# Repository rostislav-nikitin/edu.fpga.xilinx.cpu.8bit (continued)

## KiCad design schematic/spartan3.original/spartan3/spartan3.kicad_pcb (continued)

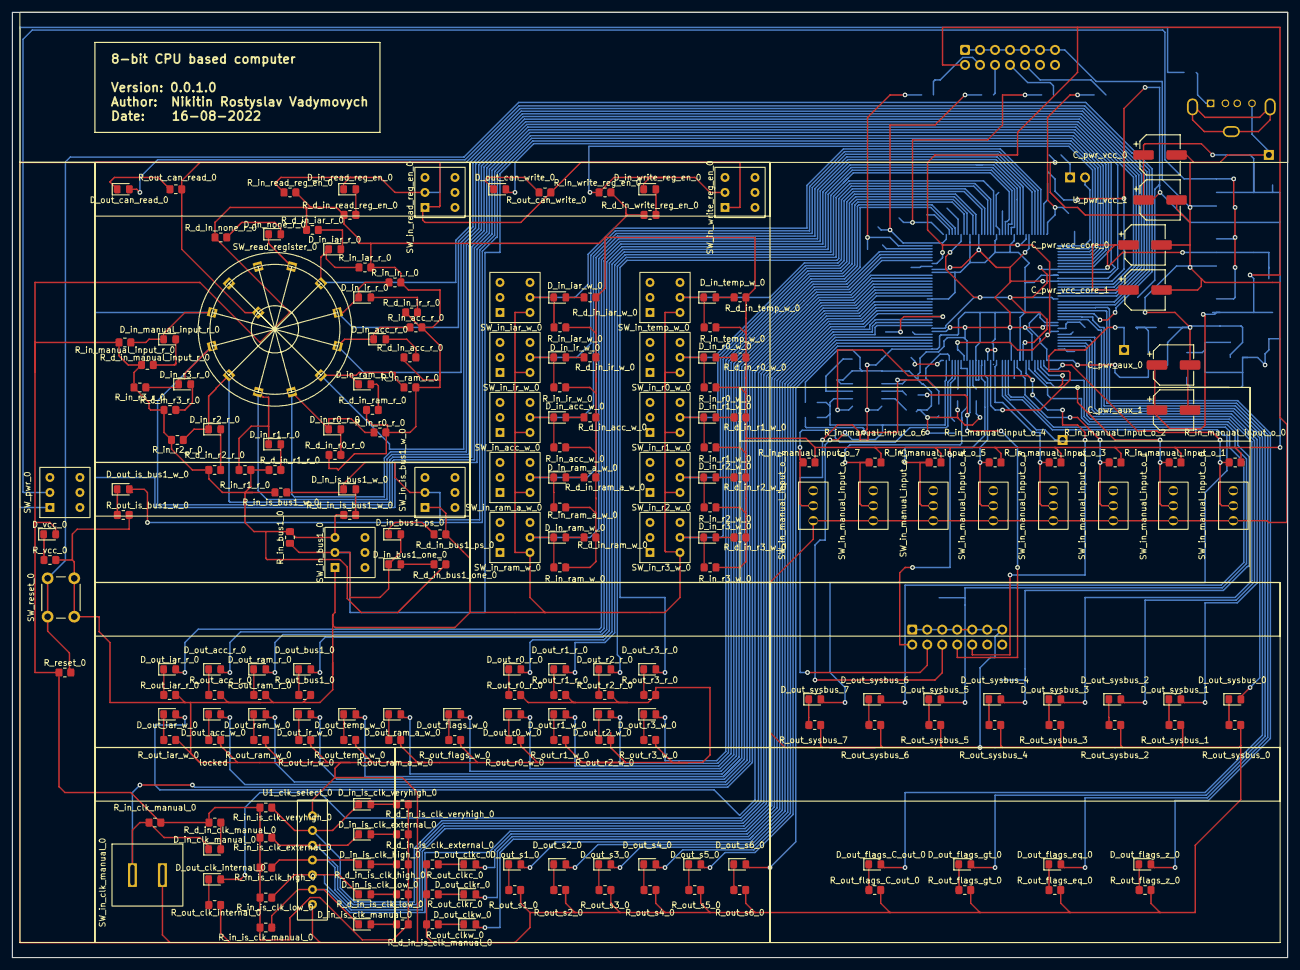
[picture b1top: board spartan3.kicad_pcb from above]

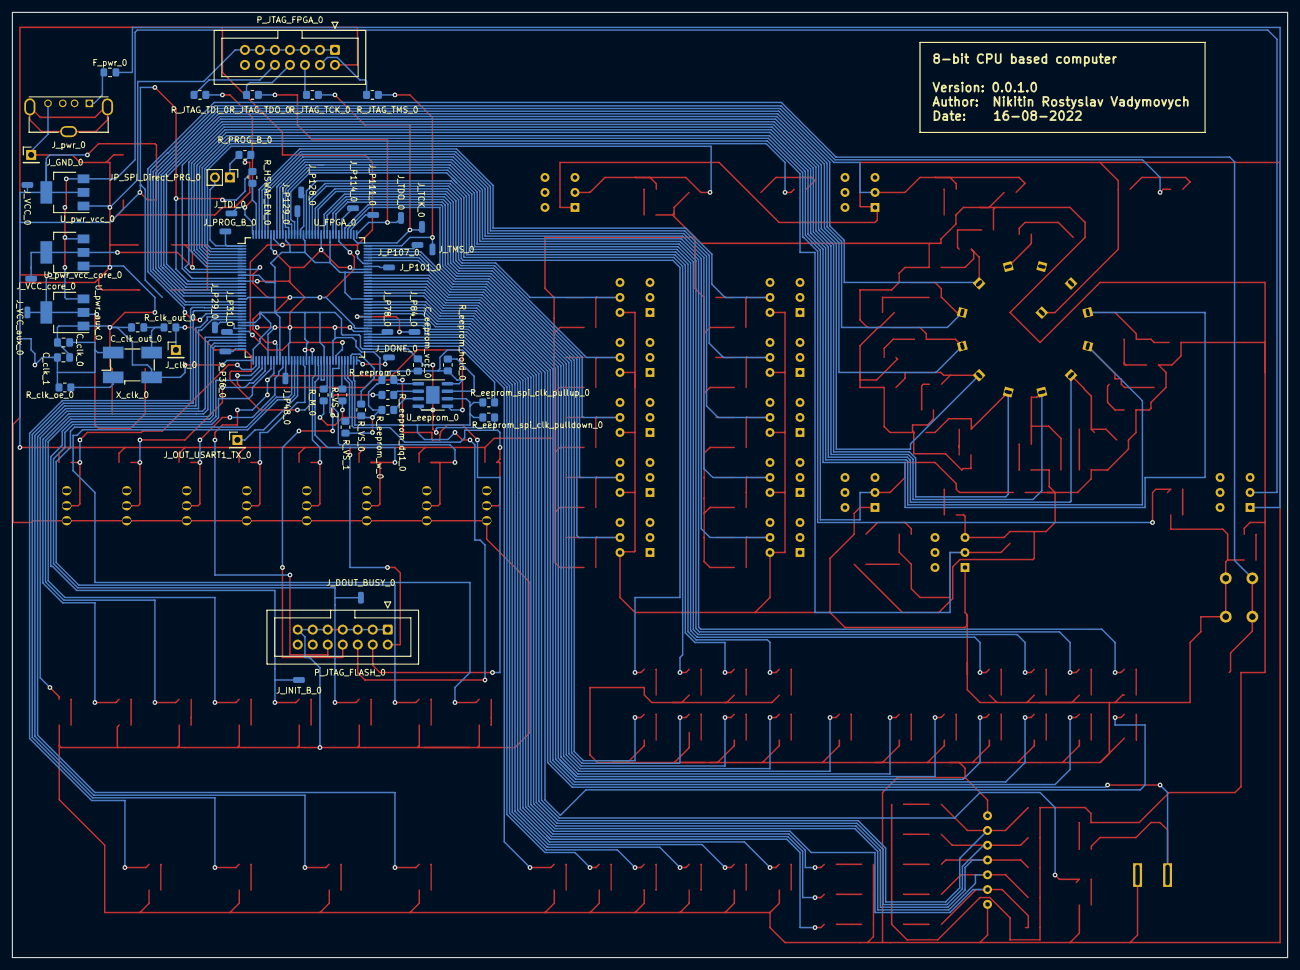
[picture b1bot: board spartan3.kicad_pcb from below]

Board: 2 copper layers, 215.9 x 160.0 mm, 282 parts (59 on the bottom side), 205 nets.

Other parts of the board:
locked: 68R; R_0805_2012Metric_Pad1.20x1.40mm_HandSolder

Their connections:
GND: locked.2; also elsewhere on the board
unnamed 42: locked.1; also elsewhere on the board

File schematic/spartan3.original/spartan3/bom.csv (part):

"null","Sourced","Placed","References","Value","Footprint"
1,"✓","","C_clk_out_0","15pF","C_0805_2012Metric_Pad1.18x1.45mm_HandSolder"
2,"✓","","C_clk_0","0.1uF","C_0805_2012Metric_Pad1.18x1.45mm_HandSolder"
3,"✓","","C_clk_1","4.7uF","C_0805_2012Metric_Pad1.18x1.45mm_HandSolder"
4,"✓","","C_pwr_aux_0","100uF","CP_Elec_6.3x5.4"
5,"✓","","C_pwr_aux_1","100uF","CP_Elec_6.3x5.4"
6,"✓","","C_pwr_vcc_0","100uF","CP_Elec_6.3x5.4"
7,"✓","","C_pwr_vcc_core_0","100uF","CP_Elec_6.3x5.4"
8,"✓","","C_pwr_vcc_core_1","100uF","CP_Elec_6.3x5.4"
9,"✓","","U_pwr_vcc_1","100uF","CP_Elec_6.3x5.4"
10,"✓","","R__eeprom_dq1_0","33R","R_0805_2012Metric_Pad1.20x1.40mm_HandSolder"
11,"✓","","R_clk_out_0","33R","R_0805_2012Metric_Pad1.20x1.40mm_HandSolder"
12,"✓","","R_JTAG_TCK_0","33R","R_0805_2012Metric_Pad1.20x1.40mm_HandSolder"
13,"✓","","R_JTAG_TDI_0","33R","R_0805_2012Metric_Pad1.20x1.40mm_HandSolder"
14,"✓","","R_JTAG_TDO_0","33R","R_0805_2012Metric_Pad1.20x1.40mm_HandSolder"
15,"✓","","R_JTAG_TMS_0","33R","R_0805_2012Metric_Pad1.20x1.40mm_HandSolder"
16,"✓","","R_d_in_acc_r_0","68R","R_0805_2012Metric_Pad1.20x1.40mm_HandSolder"
17,"✓","","R_d_in_acc_w_0","68R","R_0805_2012Metric_Pad1.20x1.40mm_HandSolder"
18,"✓","","R_d_in_bus1_one_0","68R","R_0805_2012Metric_Pad1.20x1.40mm_HandSolder"
19,"✓","","R_d_in_bus1_ps_0","68R","R_0805_2012Metric_Pad1.20x1.40mm_HandSolder"
20,"✓","","R_d_in_clk_manual_0","68R","R_0805_2012Metric_Pad1.20x1.40mm_HandSolder"
21,"✓","","R_d_in_iar_r_0","68R","R_0805_2012Metric_Pad1.20x1.40mm_HandSolder"
22,"✓","","R_d_in_iar_w_0","68R","R_0805_2012Metric_Pad1.20x1.40mm_HandSolder"
23,"✓","","R_d_in_ir_r_0","68R","R_0805_2012Metric_Pad1.20x1.40mm_HandSolder"
24,"✓","","R_d_in_ir_w_0","68R","R_0805_2012Metric_Pad1.20x1.40mm_HandSolder"
25,"✓","","R_d_in_is_bus1_w_0","68R","R_0805_2012Metric_Pad1.20x1.40mm_HandSolder"
26,"✓","","R_d_in_is_clk_external_0","68R","R_0805_2012Metric_Pad1.20x1.40mm_HandSolder"
27,"✓","","R_d_in_is_clk_high_0","68R","R_0805_2012Metric_Pad1.20x1.40mm_HandSolder"
28,"✓","","R_d_in_is_clk_low_0","68R","R_0805_2012Metric_Pad1.20x1.40mm_HandSolder"
29,"✓","","R_d_in_is_clk_manual_0","68R","R_0805_2012Metric_Pad1.20x1.40mm_HandSolder"
30,"✓","","R_d_in_is_clk_veryhigh_0","68R","R_0805_2012Metric_Pad1.20x1.40mm_HandSolder"
31,"✓","","R_d_in_manual_input_r_0","68R","R_0805_2012Metric_Pad1.20x1.40mm_HandSolder"
32,"✓","","R_d_in_none_r_0","68R","R_0805_2012Metric_Pad1.20x1.40mm_HandSolder"
33,"✓","","R_d_in_r0_r_0","68R","R_0805_2012Metric_Pad1.20x1.40mm_HandSolder"
34,"✓","","R_d_in_r0_w_0","68R","R_0805_2012Metric_Pad1.20x1.40mm_HandSolder"
35,"✓","","R_d_in_r1_r_0","68R","R_0805_2012Metric_Pad1.20x1.40mm_HandSolder"
36,"✓","","R_d_in_r1_w_0","68R","R_0805_2012Metric_Pad1.20x1.40mm_HandSolder"
37,"✓","","R_d_in_r2_r_0","68R","R_0805_2012Metric_Pad1.20x1.40mm_HandSolder"
38,"✓","","R_d_in_r2_w_0","68R","R_0805_2012Metric_Pad1.20x1.40mm_HandSolder"
39,"✓","","R_d_in_r3_r_0","68R","R_0805_2012Metric_Pad1.20x1.40mm_HandSolder"
40,"✓","","R_d_in_r3_w_0","68R","R_0805_2012Metric_Pad1.20x1.40mm_HandSolder"
41,"✓","","R_d_in_ram_a_w_0","68R","R_0805_2012Metric_Pad1.20x1.40mm_HandSolder"
42,"✓","","R_d_in_ram_r_0","68R","R_0805_2012Metric_Pad1.20x1.40mm_HandSolder"
43,"✓","","R_d_in_ram_w_0","68R","R_0805_2012Metric_Pad1.20x1.40mm_HandSolder"
44,"✓","","R_d_in_read_reg_en_0","68R","R_0805_2012Metric_Pad1.20x1.40mm_HandSolder"
45,"✓","","R_d_in_temp_w_0","68R","R_0805_2012Metric_Pad1.20x1.40mm_HandSolder"
46,"✓","","R_d_in_write_reg_en_0","68R","R_0805_2012Metric_Pad1.20x1.40mm_HandSolder"
47,"✓","","R_out_acc_r_0","68R","R_0805_2012Metric_Pad1.20x1.40mm_HandSolder"
48,"✓","","R_out_acc_w_0","68R","R_0805_2012Metric_Pad1.20x1.40mm_HandSolder"
49,"✓","","R_out_bus1_0","68R","R_0805_2012Metric_Pad1.20x1.40mm_HandSolder"
50,"✓","","R_out_can_read_0","68R","R_0805_2012Metric_Pad1.20x1.40mm_HandSolder"
51,"✓","","R_out_can_write_0","68R","R_0805_2012Metric_Pad1.20x1.40mm_HandSolder"
52,"✓","","R_out_clk_internal_0","68R","R_0805_2012Metric_Pad1.20x1.40mm_HandSolder"
53,"✓","","R_out_clkc_0","68R","R_0805_2012Metric_Pad1.20x1.40mm_HandSolder"
54,"✓","","R_out_clkr_0","68R","R_0805_2012Metric_Pad1.20x1.40mm_HandSolder"
55,"✓","","R_out_clkw_0","68R","R_0805_2012Metric_Pad1.20x1.40mm_HandSolder"
56,"✓","","R_out_flags_C_out_0","68R","R_0805_2012Metric_Pad1.20x1.40mm_HandSolder"
57,"✓","","R_out_flags_eq_0","68R","R_0805_2012Metric_Pad1.20x1.40mm_HandSolder"
58,"✓","","R_out_flags_gt_0","68R","R_0805_2012Metric_Pad1.20x1.40mm_HandSolder"
59,"✓","","R_out_flags_w_0","68R","R_0805_2012Metric_Pad1.20x1.40mm_HandSolder"
60,"✓","","R_out_flags_z_0","68R","R_0805_2012Metric_Pad1.20x1.40mm_HandSolder"
61,"✓","","R_out_iar_r_0","68R","R_0805_2012Metric_Pad1.20x1.40mm_HandSolder"
62,"✓","","R_out_iar_w_0","68R","R_0805_2012Metric_Pad1.20x1.40mm_HandSolder"
63,"✓","","R_out_ir_w_0","68R","R_0805_2012Metric_Pad1.20x1.40mm_HandSolder"
64,"✓","","R_out_is_bus1_w_0","68R","R_0805_2012Metric_Pad1.20x1.40mm_HandSolder"
65,"✓","","R_out_r0_r_0","68R","R_0805_2012Metric_Pad1.20x1.40mm_HandSolder"
66,"✓","","R_out_r0_w_0","68R","R_0805_2012Metric_Pad1.20x1.40mm_HandSolder"
67,"✓","","R_out_r1_r_0","68R","R_0805_2012Metric_Pad1.20x1.40mm_HandSolder"
68,"✓","","R_out_r1_w_0","68R","R_0805_2012Metric_Pad1.20x1.40mm_HandSolder"
69,"✓","","R_out_r2_r_0","68R","R_0805_2012Metric_Pad1.20x1.40mm_HandSolder"
70,"✓","","R_out_r2_w_0","68R","R_0805_2012Metric_Pad1.20x1.40mm_HandSolder"
71,"✓","","R_out_r3_r_0","68R","R_0805_2012Metric_Pad1.20x1.40mm_HandSolder"
72,"✓","","R_out_r3_w_0","68R","R_0805_2012Metric_Pad1.20x1.40mm_HandSolder"
73,"✓","","R_out_ram_a_w_0","68R","R_0805_2012Metric_Pad1.20x1.40mm_HandSolder"
74,"✓","","R_out_ram_r_0","68R","R_0805_2012Metric_Pad1.20x1.40mm_HandSolder"
75,"✓","","R_out_ram_w_0","68R","R_0805_2012Metric_Pad1.20x1.40mm_HandSolder"
76,"✓","","R_out_s1_0","68R","R_0805_2012Metric_Pad1.20x1.40mm_HandSolder"
77,"✓","","R_out_s2_0","68R","R_0805_2012Metric_Pad1.20x1.40mm_HandSolder"
78,"✓","","R_out_s3_0","68R","R_0805_2012Metric_Pad1.20x1.40mm_HandSolder"
79,"✓","","R_out_s4_0","68R","R_0805_2012Metric_Pad1.20x1.40mm_HandSolder"
80,"✓","","R_out_s5_0","68R","R_0805_2012Metric_Pad1.20x1.40mm_HandSolder"
81,"✓","","R_out_s6_0","68R","R_0805_2012Metric_Pad1.20x1.40mm_HandSolder"
82,"✓","","R_out_sysbus_0","68R","R_0805_2012Metric_Pad1.20x1.40mm_HandSolder"
83,"✓","","R_out_sysbus_1","68R","R_0805_2012Metric_Pad1.20x1.40mm_HandSolder"
84,"✓","","R_out_sysbus_2","68R","R_0805_2012Metric_Pad1.20x1.40mm_HandSolder"
85,"✓","","R_out_sysbus_3","68R","R_0805_2012Metric_Pad1.20x1.40mm_HandSolder"
86,"✓","","R_out_sysbus_4","68R","R_0805_2012Metric_Pad1.20x1.40mm_HandSolder"
87,"✓","","R_out_sysbus_5","68R","R_0805_2012Metric_Pad1.20x1.40mm_HandSolder"
88,"✓","","R_out_sysbus_6","68R","R_0805_2012Metric_Pad1.20x1.40mm_HandSolder"
89,"✓","","R_out_sysbus_7","68R","R_0805_2012Metric_Pad1.20x1.40mm_HandSolder"
90,"✓","","R_out_temp_w_0","68R","R_0805_2012Metric_Pad1.20x1.40mm_HandSolder"
91,"✓","","R_vcc_0","68R","R_0805_2012Metric_Pad1.20x1.40mm_HandSolder"
92,"✓","","R_eeprom_spi_clk_pulldown_0","100R","R_0805_2012Metric_Pad1.20x1.40mm_HandSolder"
93,"✓","","R_eeprom_spi_clk_pullup_0","100R","R_0805_2012Metric_Pad1.20x1.40mm_HandSolder"
94,"✓","","R_PROG_B_0","820R","R_0805_2012Metric_Pad1.20x1.40mm_HandSolder"
95,"✓","","C_eeprom_vcc_0",104,"C_0805_2012Metric_Pad1.18x1.45mm_HandSolder"
96,"✓","","R_eeprom_hold_0","10K","R_0805_2012Metric_Pad1.20x1.40mm_HandSolder"
97,"✓","","R_eeprom_s_0","10K","R_0805_2012Metric_Pad1.20x1.40mm_HandSolder"
98,"✓","","R_eeprom_w_0","10K","R_0805_2012Metric_Pad1.20x1.40mm_HandSolder"
99,"✓","","R_HSWAP_EN_0","10K","R_0805_2012Metric_Pad1.20x1.40mm_HandSolder"
100,"✓","","R_M_0","10K","R_0805_2012Metric_Pad1.20x1.40mm_HandSolder"
101,"✓","","R_VS_0","10K","R_0805_2012Metric_Pad1.20x1.40mm_HandSolder"
102,"✓","","R_VS_1","10K","R_0805_2012Metric_Pad1.20x1.40mm_HandSolder"
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
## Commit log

2022-03-28 Initial
2022-03-30 01. Registers refactored 02. LD/ST instructions implemented (not tested yet)
2022-03-31 LDC instruction implemented
2022-04-01 JMPR/JMP implemented
2022-04-02 JMPIF/CLF instructions was added
2022-04-03 01. Carry in implemented 02. ASM simple counter program implemented
2022-04-04 01. ASM counter program was updated. 02. JMPIF fixed
2022-04-08 Z buffers replaced with MUXERS. Design working in hardware
2022-04-12 Computer front panel was added
2022-04-13 Computer front panel was updated
2022-04-16 Simple cpu frequency divider was implemented
2022-04-16 Divider equation was updated
2022-04-18 Manual R0 implemented
2022-04-19 manr register support was added
2022-04-20 r0, r1, r2, r3 registers r/w updated
2022-04-21 Read/Write blocks implementation done
2022-04-21 CPU testbench updated
2022-04-22 Debug outputs was added
2022-04-24 VGA test driver was implemented
2022-04-24 VGA v2 driver was implemented
2022-04-26 Input/Output CPU PINs was renamed in a same way
2022-04-27 Manual::OK
2022-04-27 Updated to workin state
2022-04-27 Rebuid part of ICs [Working]
2022-04-28 Rebuid part of ICs/added clkc, clkr, clkw to the output [Working]
2022-04-28 Manual/Low Frequency modes was implemented [Working]
2022-05-03 Front panel design updated. Real dimesions was applied.
2022-05-03 3D box model added
2022-05-05 The front panel was updated
2022-05-08 Frontend panel updated
2022-05-10 The frontend panel updated
2022-05-12 01. The frontend panel design was updated 02. The frontend panel 3D STL model was added
2022-05-16 Frontend updated
2022-05-18 Front panel :: Small chages
2022-05-22 Working ver
2022-05-22 Working version :: Stage LEDs was added
2022-05-22 Working version :: Clock mode LEDs and manual button was added
2022-05-24 Working version :: Flags LEDs was added
2022-05-25 Working version :: Sysbus LEDs was added
2022-05-31 Working version :: Read Register block was added
2022-06-01 Working version :: CPU Control block LEDs was added
2022-06-02 Working version :: input switches was added
2022-06-03 Working version :: input switches and logic was added
2022-06-07 Working version :: Write register and bus1 LEDs was added
2022-06-07 Working version :: Writeto RAM and manual clock input debouncing was added
2022-06-08 Working version :: 1Hz/1Stg/1Inst frequency dividers was implemented & added
2022-06-09 Working version :: 1KHz frequency dividers was implemented & added
2022-06-09 Working version :: IR read implemented
2022-06-12 Working version :: Cpu control/Stepper reset was added
2022-06-12 Working version :: Dark front panel was added. Bright front panel was updated
2022-06-13 Not workin Commited
2022-06-13 Working :: version 0.1 alpha
2022-06-20 USART example was added
2022-06-20 Working :: USART was added
2022-06-21 Working :: Prepared to RAM extraction from CPU. Ports support was added
2022-06-21 Working :: RAM extracted
2022-06-22 Working :: Port one added
2022-06-22 Working :: Generator was replaced to counter based one. Port one was fixed
2022-06-24 Working :: PT/One was replaced with PT/Const
2022-06-24 Working(*) :: IN/OUT implemented
2022-06-24 Working :: IN/OUT implemented. Counter updated
2022-06-25 Working :: IN/OUT fixed. ADD 0xF0 was replaced to OR 0xF0
2022-06-25 Working :: Counter updated :: IN added
2022-06-25 Working :: Instruction set extended
2022-07-11 XC3S250E-4TQG144 version KiCAD schematics added
2022-07-12 1.CPU control & Clock blocks added. 2.Slider switch library added.
2022-07-13 Schematics :: Read Register block added
2022-07-14 Schematics :: 1.Write Register added 2.1/PS Bus added
2022-07-16 Schematic :: Power/Clock/JTAG/EEPROM schematics added
2022-07-16 Schematic :: LEDs polarity fixed/Power LED added
2022-07-18 Schematics :: footprints partially assigned
2022-07-19 Schematics :: SW Rotary 12 footprint added
2022-07-20 Schematics :: JTAG/SPST/SPDT updated
2022-07-20 Schematics :: reset added
2022-07-21 PCB layout :: Implementation process started
2022-07-22 PCB layout :: updated
2022-07-26 Schematics :: Read Register fixed -- Rs added. PCB layout :: Updated
2022-07-27 PCB layout :: reset button side swapped
2022-07-27 Schematics :: updated / PCB layout :: updated
2022-07-29 PCB layout updated
2022-08-01 PCB layout :: checked & updated
2022-08-02 Schematic :: LED R/SW_DPDT updated. PCB layout :: logic, non FPGA connections implemented
2022-08-03 Schematics :: J_CONTROL added. PCB layout :: updated
2022-08-05 Schematics :: in/out pins mapped. PCB layout :: updated
2022-08-07 Schematics :: updated. PCB layout :: updated
2022-08-09 FPGA pins mapping added/updated. Schematics/PCB layout :: updated according to the added/updated PINs mapping
2022-08-10 Tactile switch footprint updated. DRC rules checked/fixed
2022-08-10 Schematics :: power capicators added. PCB layout :: labels updated
2022-08-12 Schematics/PCB layout :: Oscilator updated, helpful PINs extracted
2022-08-15 Schematics/PCB layout/FPGA pin mapping updated. Gerber/Drill files generated
2022-08-15 Drill files updated to Metrics (istead of inches).
2022-08-15 Schematics/PCB layout updated. Gerber/Drill/BOM re-generated
2022-08-16 Rotatory12 pads holes extended. PCB layout updated
2022-09-05 The Assembly IDE development started
